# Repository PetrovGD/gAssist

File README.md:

# gAssist (WIP)

### gAssist is a portable device, which connects to your phone and gives you the most important information. It includes functions as:

* Reading notifications from smartphone
* Taking pictures from the smartphone using gAssist (Remote Camera Shutter)
* Controlling media, running on the phone (Media Controller with previous track, play/pause and next track)
* Controlling presentations (Presentation controller with Previous slide, next slide, start and end slideshow)
* Control volume (Volume Control)
* ...more in future versions

## Description
 - gAssist is an ESP32-C3 based device, utilising a 0.96inch SSD1306 OLED display for displaying menus and information. It is controlled using 5 push buttons (up, down, left, right and enter) which control menus on the display. You can use it to read your notifications, without touching your phone (This option is currently only supported on iOS); Control running media by using the Media Control menu, take photos without the need of running back to your phone using the Remote Camera shutter.
 - More functionalities are planned to be implemented.
 - It will have a 3D printed enclosure which is going to be portable and small, so you can hide it in your pocket.

## BOM (Bill of Materials)
 - 1pcs ESP32-C3-Super-Mini (Other ESP32s could be used probably, but I haven't tested yet)
 - 1 pcs SSD1306 0.96inch OLED display
 - 5pcs push-buttons
 - 1 pcs custom PCB or breadboard

## Short build guide
 - You can use the schematic below to connect the parts together on a breadboard
 - You can also use the PCB provided or create your own PCB
 - The program is coded using the Arduino framework in Platform.IO
 - All the libraries required are written in platformio.ini
 - ESP32-ANCS library is modified for the use of this project and is provided as a ZIP in the repo

## Planned implementations
 - Notifications on Android
 - Lock/Unlock switch
 - BLE connection manager (Control paired devices and switch connected device)

## Screenshots of the project

### PCB design

### Schematic

## Demo of the project

### Overview of menus
* https://youtu.be/tBosUBp-U7k
   
### Overview of notifcation menu
*  https://youtu.be/h5D4cYwPhq4

### Demo of media control
* https://youtu.be/3CNltpzKNEg

### Demo of remote camera shutter
* https://youtu.be/_CQfvp7ikwA

### Overview of new functionalities added to gAssist (Volume control and Presentation Control)
* https://youtu.be/w5ZUXPo0fjg

### Demo of presentation control on gAssist
* https://youtu.be/Z9RXJxisC2w

### Compiled binary of latest working version 
* https://github.com/PetrovGD/gAssist/releases/download/releases/firmware.bin

## The enclosure of gAssist is still unfinished so it's not uploaded here.

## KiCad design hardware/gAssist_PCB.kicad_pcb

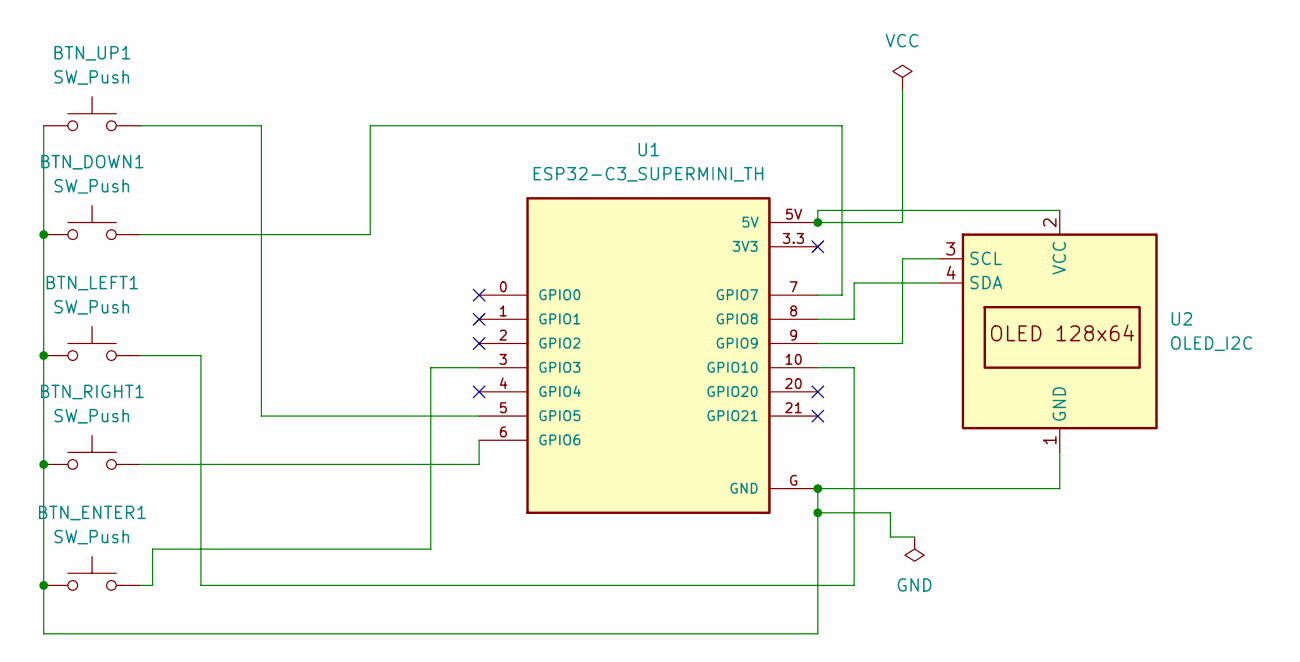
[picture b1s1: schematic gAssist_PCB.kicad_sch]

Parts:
BTN_DOWN1: SW_Push; SW_Push_1P1T_NO_E-Switch_TL3301NxxxxxG
BTN_ENTER1: SW_Push; SW_Push_1P1T_NO_E-Switch_TL3301NxxxxxG
BTN_LEFT1: SW_Push; SW_Push_1P1T_NO_E-Switch_TL3301NxxxxxG
BTN_RIGHT1: SW_Push; SW_Push_1P1T_NO_E-Switch_TL3301NxxxxxG
BTN_UP1: SW_Push; SW_Push_1P1T_NO_E-Switch_TL3301NxxxxxG
U1: ESP32-C3_SUPERMINI_TH; MODULE_ESP32-C3_SUPERMINI; MPN ESP32-C3 SuperMini_TH
U2: OLED_I2C; OLED_SSD1306_I2C_0.96

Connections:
unnamed: BTN_DOWN1.1, BTN_ENTER1.1, BTN_LEFT1.1, BTN_RIGHT1.1, BTN_UP1.1, U1.G (GND), U2.1 (GND)
unnamed: BTN_ENTER1.2, U1.3 (GPIO3)
unnamed: BTN_UP1.2, U1.5 (GPIO5)
unnamed: BTN_RIGHT1.2, U1.6 (GPIO6)
unnamed: BTN_DOWN1.2, U1.7 (GPIO7)
unnamed: U1.8 (GPIO8), U2.4 (SDA)
unnamed: U1.9 (GPIO9), U2.3 (SCL)
unnamed: BTN_LEFT1.2, U1.10 (GPIO10)
unnamed: U1.5V, U2.2 (VCC)

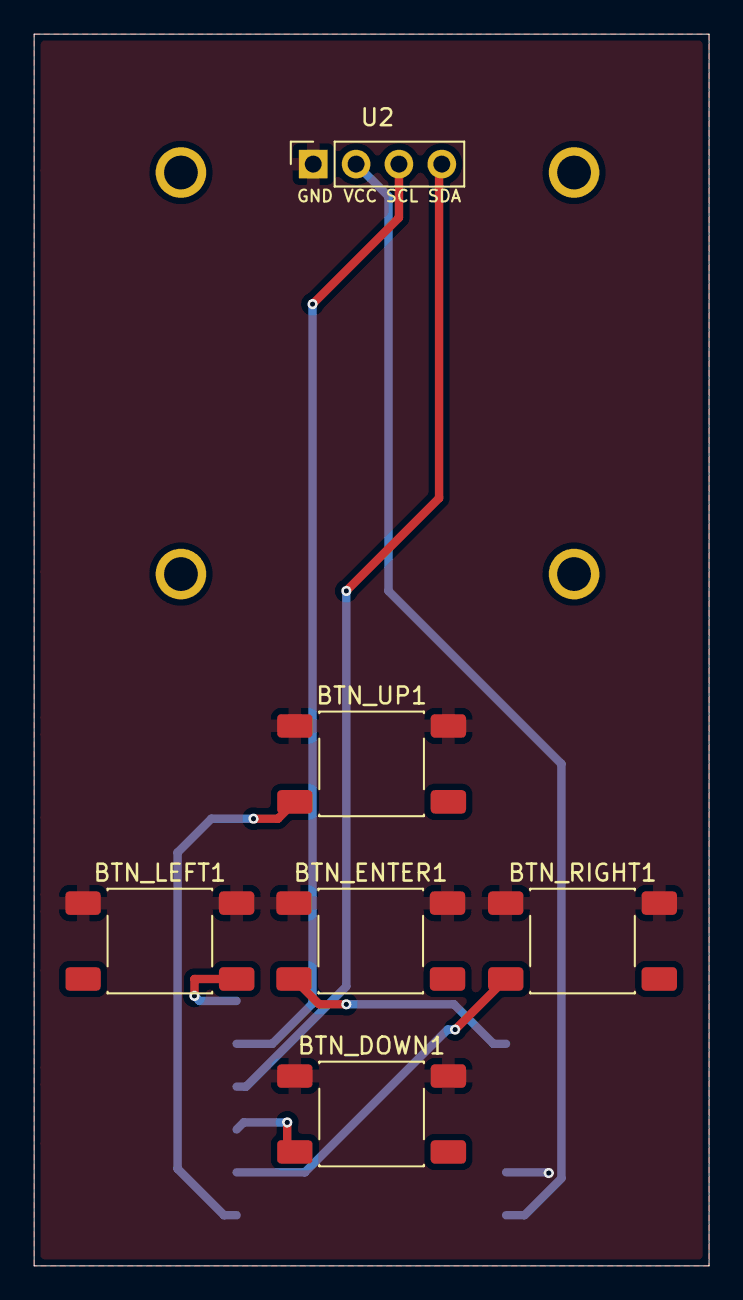
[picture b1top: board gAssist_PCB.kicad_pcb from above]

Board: 2 copper layers, 40.0 x 73.0 mm, 7 parts (1 on the bottom side), 9 nets.
